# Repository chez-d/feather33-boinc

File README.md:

# feather33-boinc
spi breakout with other stuff

Turns out you can't boot off MMC1 with the A33. This is a small 'workaround' breakout for the feather33.
Costs like 2$ from OSHpark.

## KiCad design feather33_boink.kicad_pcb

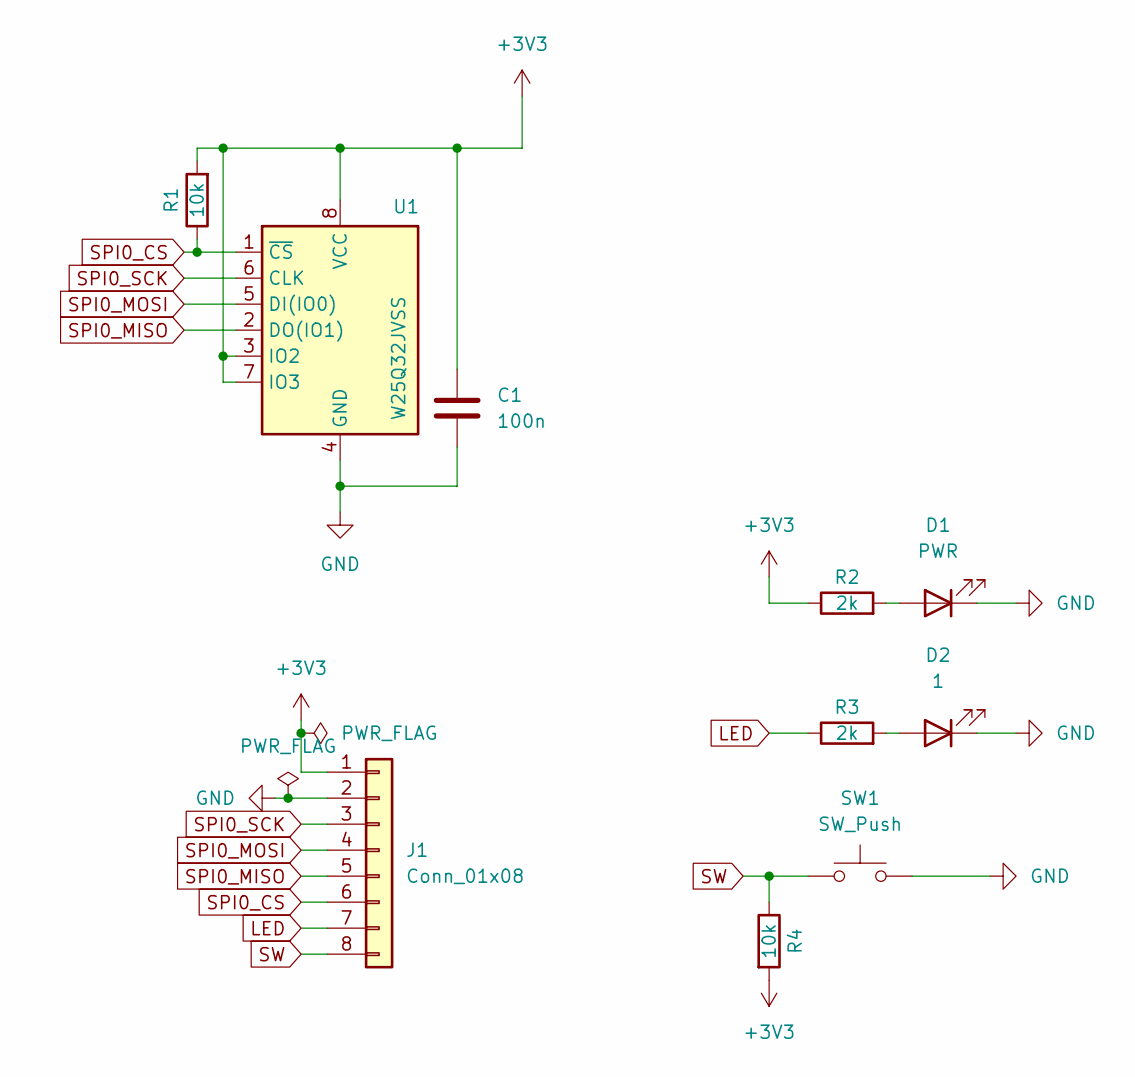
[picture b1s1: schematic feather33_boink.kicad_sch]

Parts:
C1: 100n; C_0402_1005Metric_Pad0.74x0.62mm_HandSolder
D1: PWR; LED_0603_1608Metric_Pad1.05x0.95mm_HandSolder
D2: 1; LED_0603_1608Metric_Pad1.05x0.95mm_HandSolder
J1: Conn_01x08; PinHeader_1x08_P2.54mm_Vertical
R1, R4: 10k; R_0402_1005Metric_Pad0.72x0.64mm_HandSolder
R2, R3: 2k; R_0402_1005Metric_Pad0.72x0.64mm_HandSolder
SW1: SW_Push; SW_SPST_PTS810
U1: W25Q32JVSS; SOIC-8_5.23x5.23mm_P1.27mm

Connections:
+3V3: C1.2, J1.1, R1.2, R2.1, R4.2, U1.3 (IO2), U1.7 (IO3), U1.8 (VCC)
GND: C1.1, D1.1 (K), D2.1 (K), J1.2, SW1.1, U1.4 (GND)
LED: J1.7, R3.1
unnamed: D1.2 (A), R2.2
unnamed: D2.2 (A), R3.2
SPI0_CS: J1.6, R1.1, U1.1 (~CS)
SPI0_MISO: J1.5, U1.2 (DO(IO1))
SPI0_MOSI: J1.4, U1.5 (DI(IO0))
SPI0_SCK: J1.3, U1.6 (CLK)
SW: J1.8, R4.1, SW1.2

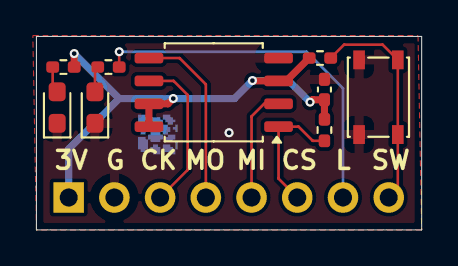
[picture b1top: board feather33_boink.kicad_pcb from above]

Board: 2 copper layers, 21.4 x 10.8 mm, 10 parts (0 on the bottom side), 10 nets.
